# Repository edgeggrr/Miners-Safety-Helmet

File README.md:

# Miners-Safety-Helmet

An IoT-based wearable safety helmet designed to enhance underground miner safety
through multi-sensor hazard detection, real-time audio-visual alerts, and cloud 
telemetry via ThingSpeak.

------------------------------------------------------------------------------
TABLE OF CONTENTS
------------------------------------------------------------------------------
1. Overview & Objectives
2. Key Features
3. Hardware Architecture & Components
4. Firmware & Software Details
5. Pin Mapping & Circuitry
6. System Workflow & Hazard Logic
7. PCB Design & Hardware Layout
8. Installation & Setup Guide
9. Testing & Validation Results
10. Future Enhancements
11. Project Team & Acknowledgments
12. References

------------------------------------------------------------------------------
1. OVERVIEW & OBJECTIVES
------------------------------------------------------------------------------
Underground mining involves extreme working conditions where hazardous gas leaks,
high temperature/humidity, sudden impacts/falls, and low overhead clearance pose
severe threats to human life. 

Objectives:
- Provide clear, immediate audio-visual alerts (buzzer chimes & flashing LED) 
  tailored for all workers, including illiterate miners.
- Integrate multi-sensor environmental and motion monitoring into a lightweight,
  wearable, low-cost helmet.
- Deliver real-time cloud data logging via ThingSpeak for supervisory oversight
  and remote safety management.

------------------------------------------------------------------------------
2. KEY FEATURES
------------------------------------------------------------------------------
- Environmental Sensing: High-accuracy temperature and humidity monitoring.
- Combustible Gas Detection: Real-time monitoring of dangerous gas/smoke levels.
- Motion & Impact Tracking: IMU-based 6-axis accelerometer and gyroscope tracking
  with complementary filtering to detect sudden tilts or impacts.
- Overhead Clearance Warnings: Ultrasonic distance detection to warn of low ceiling 
  hazards in tight shafts.
- Accessible Audio-Visual Alarms: High-frequency buzzer tones and blinking LED patterns.
- Manual SOS & Reset Controls: Tactile push-buttons for manual emergency activation 
  and alert reset with software debouncing.
- IoT Cloud Telemetry: Automatic Wi-Fi data upload to ThingSpeak every 15 seconds.

------------------------------------------------------------------------------
3. HARDWARE ARCHITECTURE & COMPONENTS
------------------------------------------------------------------------------
- Microcontroller: Espressif ESP32-S3 WROOM / ESP32 Development Board
  (Integrated Wi-Fi, ADC channels, native I2C support)
- Temperature & Humidity Sensor: DHT22 (Precision digital sensor)
- Combustible Gas Sensor: MQ-2 Gas Module (Smoke, CO, LPG detection)
- Motion & Inertial Sensor: MPU6050 6-Axis IMU (Accelerometer + Gyroscope)
- Proximity / Distance Sensor: HC-SR04 Ultrasonic Sensor
- Alert Outputs: Active Piezo Buzzer & High-Brightness LED
- Manual Controls: 2x Tactile Push-Buttons (Trigger SOS / Reset)
- Power Management: Rechargeable Battery Module & LDO Voltage Regulator

------------------------------------------------------------------------------
4. FIRMWARE & SOFTWARE DETAILS
------------------------------------------------------------------------------
- Language / Framework: C++ / Arduino Framework for ESP32
- Key Libraries:
  * WiFi.h & Wire.h (ESP32 Built-in)
  * ThingSpeak.h (ThingSpeak Communication)
  * DHT.h (Adafruit DHT Sensor Library)
  * Adafruit_MPU6050.h & Adafruit_Sensor.h (Adafruit MPU6050 Driver)

Data Filter Algorithm:
- Complementary Filter applied to MPU6050 readings:
  tiltDeg = 0.98 * gyroTilt + 0.02 * accelTilt
  (Distinguishes dynamic jerk/vibration from sustained tilt/impacts).

------------------------------------------------------------------------------
5. PIN MAPPING & CIRCUITRY
------------------------------------------------------------------------------
Component           | Module Pin | ESP32 GPIO / Pin Code
--------------------|------------|----------------------
DHT22 Temp/Hum      | DATA       | GPIO 2 (D0)
MQ-2 Gas Sensor     | AOUT       | GPIO 3 (D1 / ADC1)
Piezo Buzzer        | Positive   | GPIO 8 (D8)
Status LED          | Anode      | GPIO 10 (D10)
Manual Trigger SOS  | Pin        | GPIO 5 (D3 - INPUT_PULLUP)
Alarm Reset Button  | Pin        | GPIO 9 (D9 - INPUT_PULLUP)
HC-SR04 Ultrasonic  | TRIG       | GPIO 4 (D2)
HC-SR04 Ultrasonic  | ECHO       | GPIO 6 (D4)
MPU6050 IMU         | SDA        | GPIO 6 (D4)
MPU6050 IMU         | SCL        | GPIO 7 (D5)

------------------------------------------------------------------------------
6. SYSTEM WORKFLOW & HAZARD LOGIC
------------------------------------------------------------------------------
Sensors are sampled every 500ms. An alarm state triggers if ANY of the 
following thresholds are exceeded:

Parameter              | Threshold Level
-----------------------|------------------------------------
Temperature            | > 35.0 °C
Humidity               | > 80.0 %
Gas Concentration      | > 1800 Raw ADC Value
Tilt Angle             | > 50.0 Degrees
Overhead Clearance     | < 30.0 cm ( sustained for > 30 mins )
Manual SOS Trigger     | Button Pressed (LOW)

Cloud Upload:
- Upload Interval: Every 15 seconds to ThingSpeak.
- Fields Map:
  Field 1: Temperature (°C)
  Field 2: Humidity (%)
  Field 3: Gas Raw Reading
  Field 4: Calculated Tilt Angle (Degrees)
  Field 5: Clearance Distance (cm)
  Field 6: Hazard Alarm State (1 = Active, 0 = Normal)
  Field 7: Manual Alarm State (1 = Active, 0 = Off)

------------------------------------------------------------------------------
7. PCB DESIGN & HARDWARE LAYOUT
------------------------------------------------------------------------------
- Two-layer custom PCB designed using Altium Designer / KiCad.
- Features solid ground plane pour on top and bottom layers for noise immunity.
- Short I2C traces to avoid clock jitter and signal attenuation.
- Isolated high-frequency/noisy routing from analog sensor traces.
- Keep-out zone maintained under ESP32 PCB antenna to optimize Wi-Fi range.

------------------------------------------------------------------------------
8. INSTALLATION & SETUP GUIDE
------------------------------------------------------------------------------
1. Prerequisites:
   - Install Arduino IDE (v2.0 or higher recommended).
   - Install ESP32 Board Manager core in Arduino IDE.
   - Install required libraries: `DHT sensor library`, `Adafruit MPU6050`, 
     `Adafruit Unified Sensor`, `ThingSpeak`.

2. Configuration:
   - Open `miner_safety_helmet.ino`.
   - Update Wi-Fi Credentials:
     const char* ssid = "YOUR_WIFI_SSID";
     const char* password = "YOUR_WIFI_PASSWORD";
   - Update ThingSpeak Credentials:
     unsigned long channelID = YOUR_CHANNEL_ID;
     const char* writeAPIKey = "YOUR_WRITE_API_KEY";

3. Uploading Firmware:
   - Connect ESP32 board via USB.
   - Select correct COM Port and Board model (e.g., ESP32 Dev Module / ESP32-S3).
   - Compile and upload the sketch.

------------------------------------------------------------------------------
9. TESTING & VALIDATION RESULTS
------------------------------------------------------------------------------
- Environmental Chamber Testing: Successfully triggered alerts at > 35°C and 
  elevated smoke exposure.
- Motion Simulation: Complementary filter correctly filtered high-frequency 
  jerks while catching sustained tilt (>50°).
- Distance Validation: Accurate proximity alerts up to 30 cm clearance limit.
- Cloud Integration: Continuous 24-hour test verified 99.8% successful payload 
  delivery to ThingSpeak.

------------------------------------------------------------------------------
12. REFERENCES
------------------------------------------------------------------------------
- IEEE Xplore: "IoT-Enabled Safety Helmet for Coal Miners" 
  (https://ieeexplore.ieee.org/document/10561018/)
- KSCST Project Reports: "An IoT Based Smart Helmet for Industrial And Mining Workers"
- IJRASET: "IOT Mining Tracking & Worker Safety Helmet" (2024)
- Random Nerd Tutorials: "ESP32 Publish Sensor Readings to ThingSpeak"
==============================================================================

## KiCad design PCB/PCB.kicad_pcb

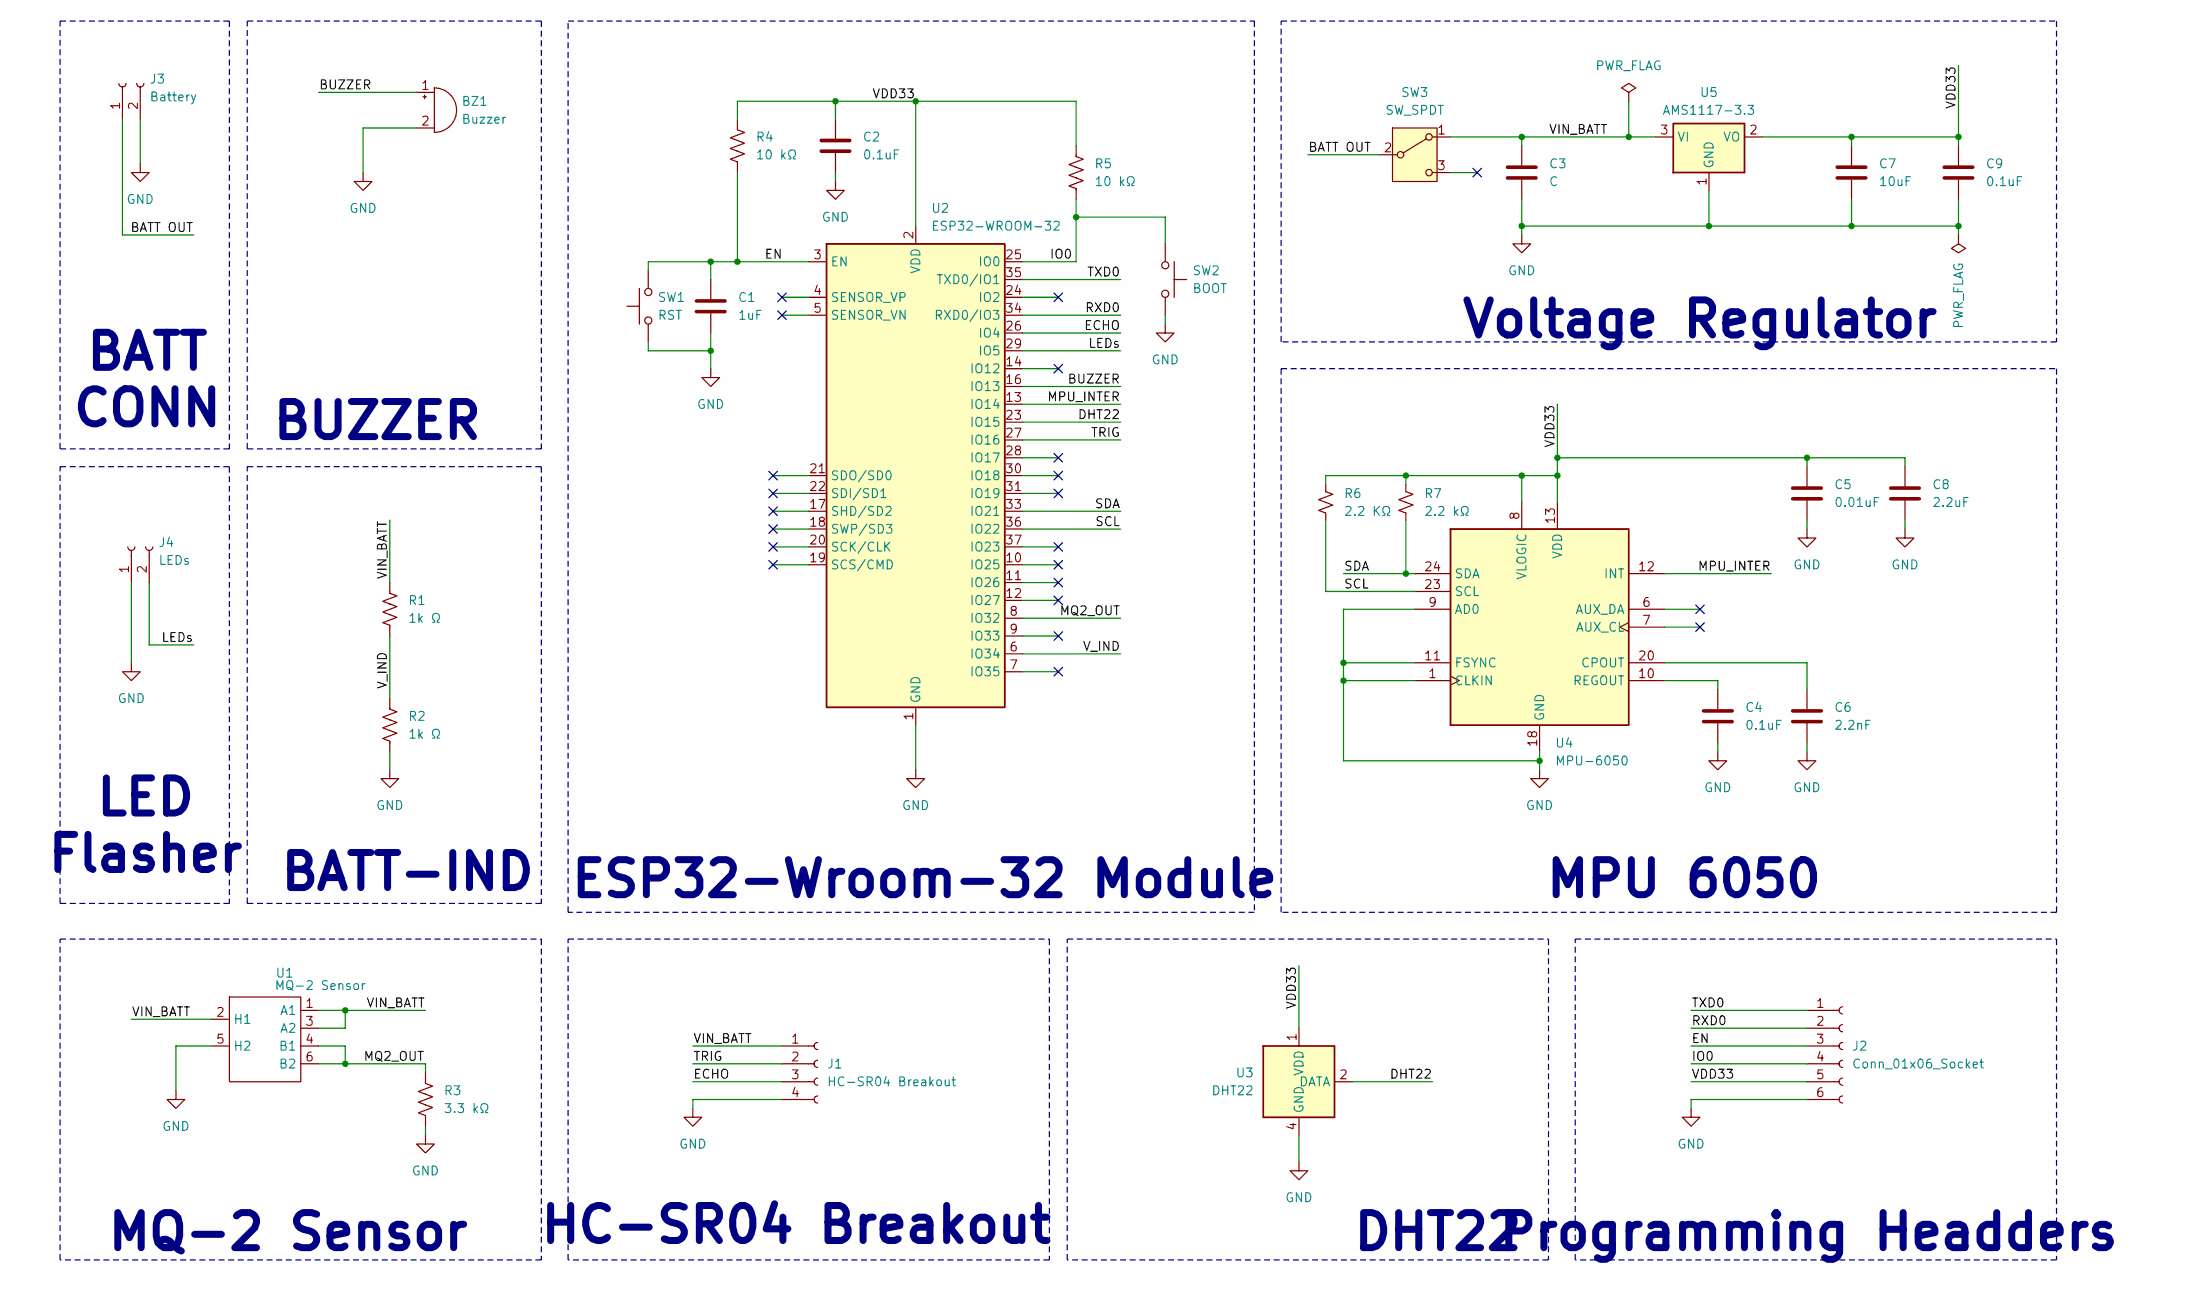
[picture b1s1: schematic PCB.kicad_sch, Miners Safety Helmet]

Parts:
BZ1: Buzzer; Buzzer_D14mm_H7mm_P10mm
C1: 1uF; C_0603_1608Metric
C2, C4, C9: 0.1uF; C_0603_1608Metric
C3: C; C_0603_1608Metric
C5: 0.01uF; C_0603_1608Metric
C6: 2.2nF; C_0603_1608Metric
C7: 10uF; C_0603_1608Metric
C8: 2.2uF; C_0603_1608Metric
J1: HC-SR04 Breakout; PinSocket_1x04_P2.54mm_Vertical
J2: Conn_01x06_Socket; PinSocket_1x06_P2.54mm_Vertical
J3: Battery; JST_EH_S2B-EH_1x02_P2.50mm_Horizontal
J4: LEDs; JST_PH_S2B-PH-K_1x02_P2.00mm_Horizontal
R1, R2: 1k Ω; R_0603_1608Metric
R3: 3.3 kΩ; R_0603_1608Metric
R4, R5: 10 kΩ; R_0603_1608Metric
R6: 2.2 KΩ; R_0603_1608Metric
R7: 2.2 kΩ; R_0603_1608Metric
SW1: RST; SW_Push_1P1T_NO_CK_KMR2
SW2: BOOT; SW_Push_1P1T_NO_CK_KMR2
SW3: SW_SPDT; SW_Slide_SPDT_Angled_CK_OS102011MA1Q
U1: MQ-2 Sensor; MQ2
U2: ESP32-WROOM-32
U3: DHT22; DHT22_Horizontal
U4: MPU-6050; InvenSense_QFN-24_4x4mm_P0.5mm
U5: AMS1117-3.3; SOT-223-3_TabPin2

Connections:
/BATT OUT: J3.1, SW3.2 (B)
/BUZZER: BZ1.1 (+), U2.16 (IO13)
/DHT22: U2.23 (IO15), U3.2 (DATA)
/ECHO: J1.3, U2.26 (IO4)
/EN: C1.1, J2.3, R4.1, SW1.2, U2.3 (EN)
/IO0: J2.4, R5.1, SW2.1, U2.25 (IO0)
/LEDs: J4.2, U2.29 (IO5)
/MPU_INTER: U2.13 (IO14), U4.12 (INT)
/MQ2_OUT: R3.2, U1.4 (B1), U1.6 (B2), U2.8 (IO32)
/RXD0: J2.2, U2.34 (RXD0/IO3)
/SCL: R6.2, U2.36 (IO22), U4.23 (SCL)
/SDA: R7.2, U2.33 (IO21), U4.24 (SDA)
/TRIG: J1.2, U2.27 (IO16)
/TXD0: J2.1, U2.35 (TXD0/IO1)
/VDD33: C2.1, C5.1, C7.1, C8.1, C9.1, J2.5, R4.2, R5.2, R6.1, R7.1, U2.2 (VDD), U3.1 (VDD), U4.8 (VLOGIC), U4.13 (VDD), U5.2 (VO)
/VIN_BATT: C3.1, J1.1, R1.1, SW3.1 (A), U1.1 (A1), U1.2 (H1), U1.3 (A2), U5.3 (VI)
/V_IND: R1.2, R2.1, U2.6 (IO34)
GND: BZ1.2 (-), C1.2, C2.2, C3.2, C4.2, C5.2, C6.2, C7.2, C8.2, C9.2, J1.4, J2.6, J3.2, J4.1, R2.2, R3.1, SW1.1, SW2.2, U1.5 (H2), U2.1 (GND), U2.15 (GND), U2.38 (GND), U2.39 (GND), U3.4 (GND), U4.1 (CLKIN), U4.9 (AD0), U4.11 (FSYNC), U4.18 (GND), U5.1 (GND)
unnamed: C6.1, U4.20 (CPOUT)
unnamed: C4.1, U4.10 (REGOUT)

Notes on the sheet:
MPU 6050
BUZZER
HC-SR04 Breakout
ESP32-Wroom-32 Module
Programming Headders
DHT22
MQ-2 Sensor
Voltage Regulator
BATT-IND
BATT CONN
LED Flasher

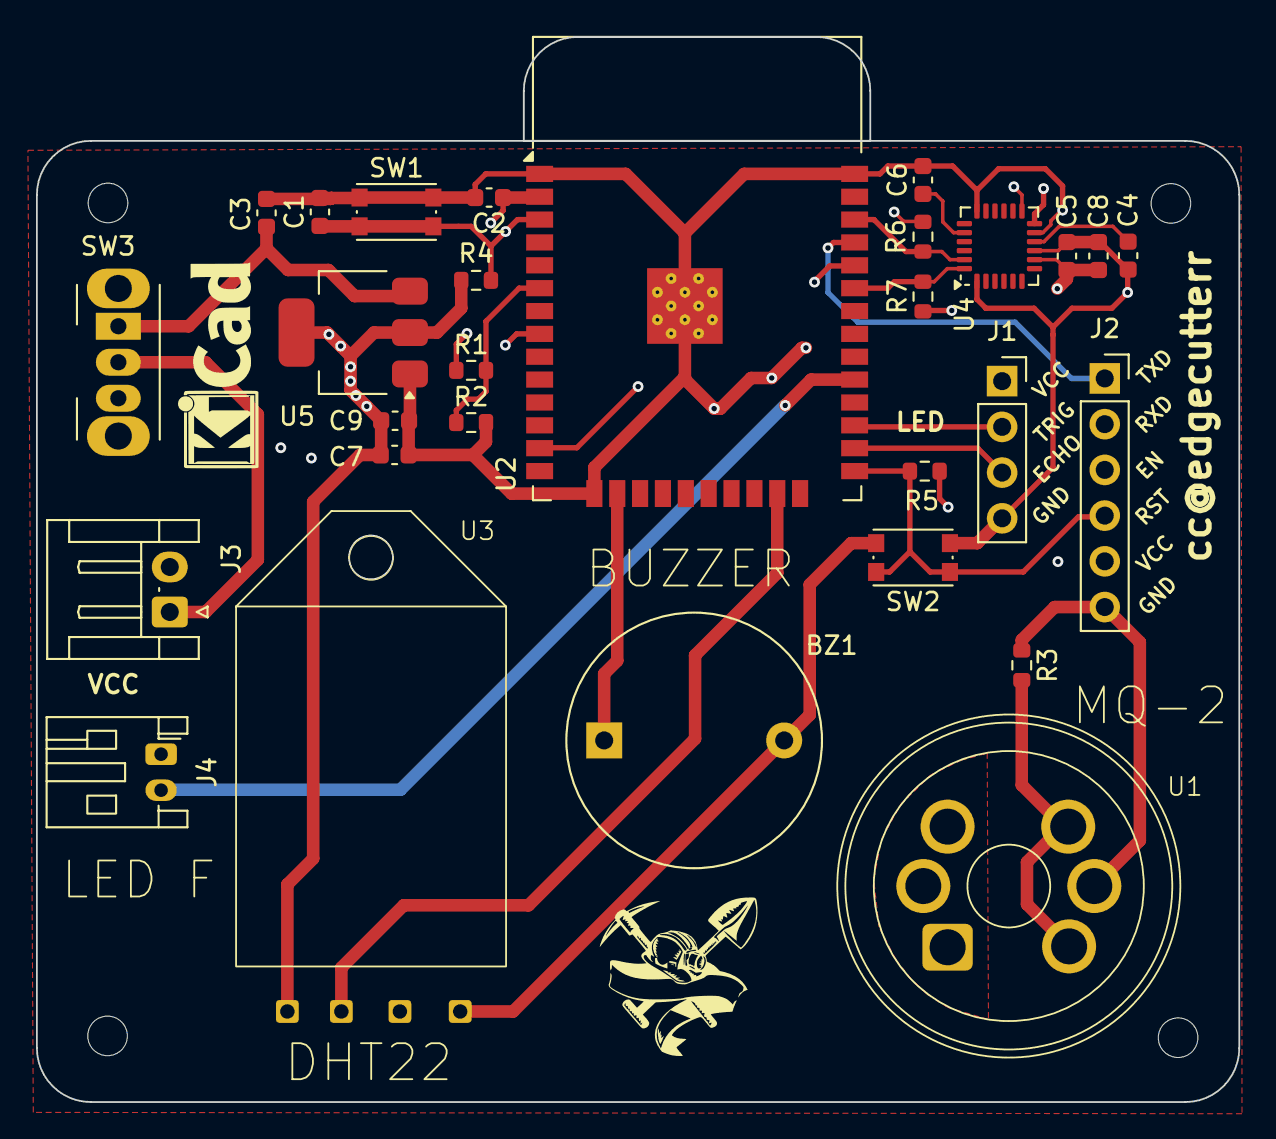
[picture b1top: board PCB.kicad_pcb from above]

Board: 4 copper layers, 66.8 x 53.4 mm, 29 parts (0 on the bottom side), 20 nets.
